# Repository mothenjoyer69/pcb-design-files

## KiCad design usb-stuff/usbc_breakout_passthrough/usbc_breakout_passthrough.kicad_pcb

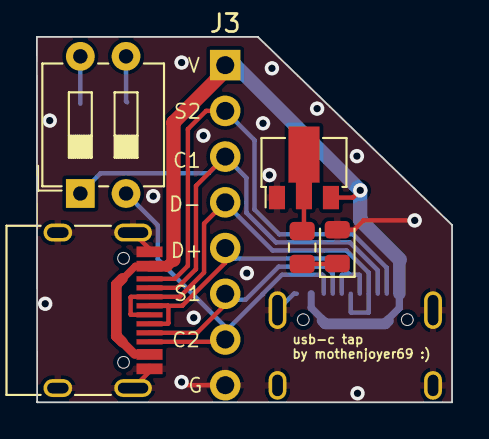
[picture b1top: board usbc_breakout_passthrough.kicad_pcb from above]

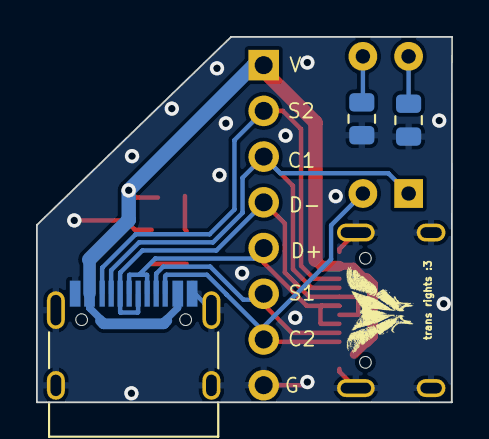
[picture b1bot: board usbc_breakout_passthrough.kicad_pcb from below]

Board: 2 copper layers, 23.1 x 20.3 mm, 9 parts (3 on the bottom side), 12 nets.

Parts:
D1: LED; LED_0805_2012Metric
J1, J2: USB_C_Receptacle; USB_C_Receptacle_HRO_TYPE-C-31-M-12
J3: Conn_01x08_Pin; PinHeader_1x08_P2.54mm_Vertical
R1, R2: 5.1k; R_0805_2012Metric
R3: 2.2k; R_0805_2012Metric
SW1: SW_DIP_x02; SW_DIP_SPSTx02_Slide_6.7x6.64mm_W7.62mm_P2.54mm_LowProfile
U1: AZ1117-3.3; SOT-89-3

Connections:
/CC1: J1.A5 (CC1), J2.A5 (CC1), J3.3, SW1.1
/CC2: J1.B5 (CC2), J2.B5 (CC2), J3.7, SW1.2
/SBU1: J1.A8 (SBU1), J2.A8 (SBU1), J3.6
/SBU2: J1.B8 (SBU2), J2.B8 (SBU2), J3.2
/USB_N-: J1.A7 (D-), J1.B7 (D-), J2.A7 (D-), J2.B7 (D-), J3.4
/USB_P+: J1.A6 (D+), J1.B6 (D+), J2.A6 (D+), J2.B6 (D+), J3.5
/VBUS: J1.A4 (VBUS), J1.A9 (VBUS), J1.B4 (VBUS), J1.B9 (VBUS), J2.A4 (VBUS), J2.A9 (VBUS), J2.B4 (VBUS), J2.B9 (VBUS), J3.1, U1.3 (VI)
GND: D1.2 (A), J1.A1 (GND), J1.A12 (GND), J1.B1 (GND), J1.B12 (GND), J1.S1 (SHIELD), J2.A1 (GND), J2.A12 (GND), J2.B1 (GND), J2.B12 (GND), J2.S1 (SHIELD), J3.8, R1.2, R2.2, U1.1 (GND)
unnamed: D1.1 (K), R3.2
unnamed: R1.1, SW1.3
unnamed: R2.1, SW1.4
unnamed: R3.1, U1.2 (VO)
